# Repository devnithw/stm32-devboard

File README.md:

# STM32 Development board

This project contains KiCAD project files for a custom STM32 development board PCB which uses the STM32F103C8Tx microcontroller.

## Schematic design
The PCB schematic file for development board is contained in the file `stm32_board.kicad_sch`. The following is a screenshot of the schematic. 

The development board uses the `STM32F103C8Tx` microcontroller. USB interface is used for both power supply and serial communication. The power fdrom the USB interface is regulated to +3.3V using the regulator circuit. An High Speed External clock is used for 16 MHz operation. The board includes pin header ports for UART and I2C communication also.

## PCB design
The PCB layout file for the circuit is contained in `stm32_board.kicad_pcb` file. Below is the screenshot of the final PCB layout after routing. I have included mounting holes for the board to be mounted onto a enclosure. The footprints for most of the components have been used from the KiCAD library itself. 3D view for the USB port was downloaded from the manufaturer's website as a step file. It is included in the file `629105150521 (rev1).stp`. I have added male headers for the UART, Serial Wire Debug and I2C communication ports. These can be configured using the STM32 Cube IDE software. 

Shown below is the 3D view of the routed and finalized PCB.

This project was done following the Udemy course by Philip Salmony. [Reference](https://www.udemy.com/course/learn-kicad-v6-and-stm32-hardware-design/)

## Technologies Used
- KiCAD V7
- STM32

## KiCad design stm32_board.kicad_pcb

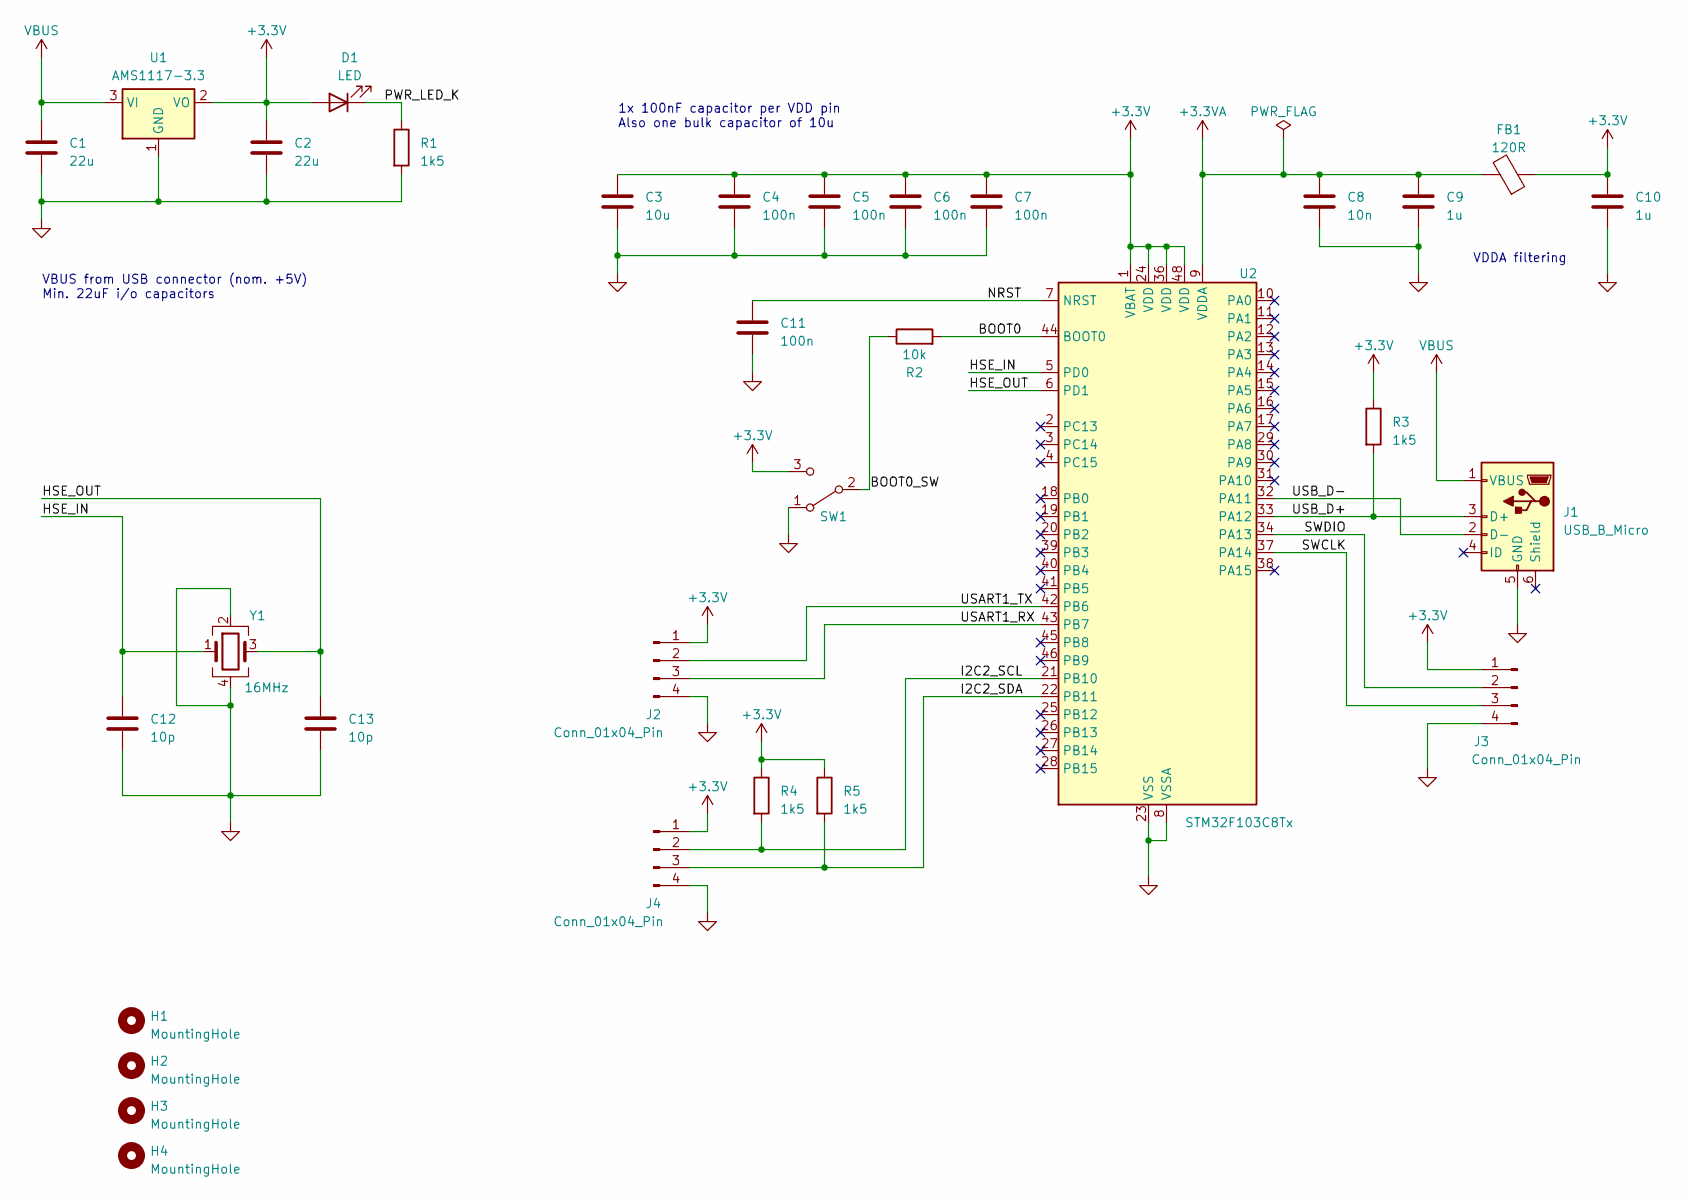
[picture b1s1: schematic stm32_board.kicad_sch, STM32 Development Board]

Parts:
C1, C2: 22u; C_0805_2012Metric
C3: 10u; C_0603_1608Metric
C4, C5, C6, C7, C11: 100n; C_0402_1005Metric
C8: 10n; C_0402_1005Metric
C9, C10: 1u; C_0402_1005Metric
C12, C13: 10p; C_0402_1005Metric
D1: LED; LED_0603_1608Metric
FB1: 120R; L_0603_1608Metric
H1, H2, H3, H4: MountingHole; MountingHole_2.2mm_M2
J1: USB_B_Micro; USB_Micro-B_Wuerth_629105150521
J2, J3, J4: Conn_01x04_Pin; PinHeader_1x04_P2.54mm_Vertical
R1, R3, R4, R5: 1k5; R_0402_1005Metric
R2: 10k; R_0402_1005Metric
SW1: SW_SPDT; SW_SPDT_PCM12
U1: AMS1117-3.3; SOT-223-3_TabPin2
U2: STM32F103C8Tx; LQFP-48_7x7mm_P0.5mm
Y1: 16MHz; Crystal_SMD_3225-4Pin_3.2x2.5mm

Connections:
+3.3V: C2.1, C3.1, C4.1, C5.1, C6.1, C7.1, C10.1, D1.2 (A), FB1.1, J2.1, J3.1, J4.1, R3.1, R4.1, R5.1, SW1.3 (C), U1.2 (VO), U2.1 (VBAT), U2.24 (VDD), U2.36 (VDD), U2.48 (VDD)
+3.3VA: C8.1, C9.1, FB1.2, U2.9 (VDDA)
/BOOT0: R2.2, U2.44 (BOOT0)
/BOOT0_SW: R2.1, SW1.2 (B)
/HSE_IN: C12.1, U2.5 (PD0), Y1.1
/HSE_OUT: C13.1, U2.6 (PD1), Y1.3
/I2C2_SCL: J4.2, R4.2, U2.21 (PB10)
/I2C2_SDA: J4.3, R5.2, U2.22 (PB11)
/NRST: C11.1, U2.7 (NRST)
/PWR_LED_K: D1.1 (K), R1.1
/SWCLK: J3.3, U2.37 (PA14)
/SWDIO: J3.2, U2.34 (PA13)
/USART1_RX: J2.3, U2.43 (PB7)
/USART1_TX: J2.2, U2.42 (PB6)
/USB_D+: J1.3 (D+), R3.2, U2.33 (PA12)
/USB_D-: J1.2 (D-), U2.32 (PA11)
GND: C1.2, C2.2, C3.2, C4.2, C5.2, C6.2, C7.2, C8.2, C9.2, C10.2, C11.2, C12.2, C13.2, J1.5 (GND), J2.4, J3.4, J4.4, R1.2, SW1.1 (A), U1.1 (GND), U2.8 (VSSA), U2.23 (VSS), U2.35 (VSS), U2.47 (VSS), Y1.2, Y1.4
VBUS: C1.1, J1.1 (VBUS), U1.3 (VI)

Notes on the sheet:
1x 100nF capacitor per VDD pin Also one bulk capacitor of 10u
VBUS from USB connector (nom. +5V) Min. 22uF i/o capacitors
VDDA filtering

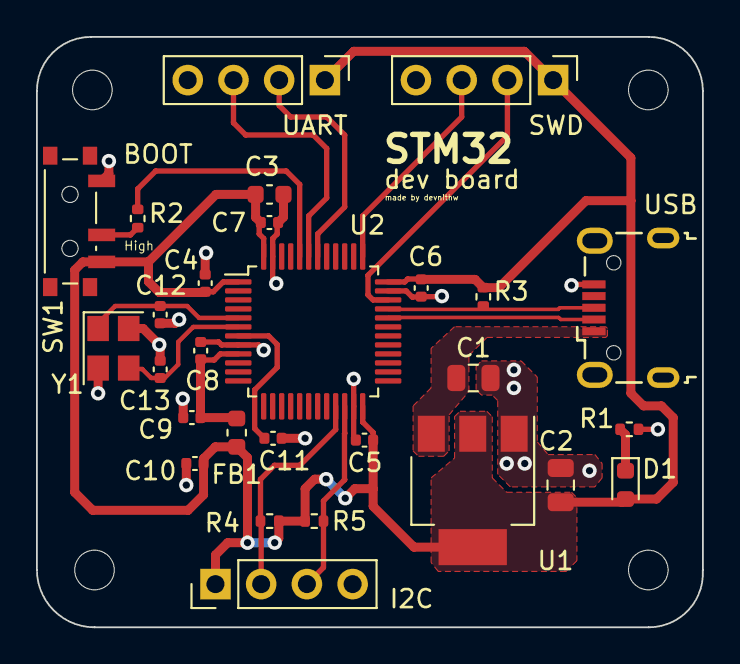
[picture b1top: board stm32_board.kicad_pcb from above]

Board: 2 copper layers, 37.0 x 32.8 mm, 32 parts (0 on the bottom side), 18 nets.

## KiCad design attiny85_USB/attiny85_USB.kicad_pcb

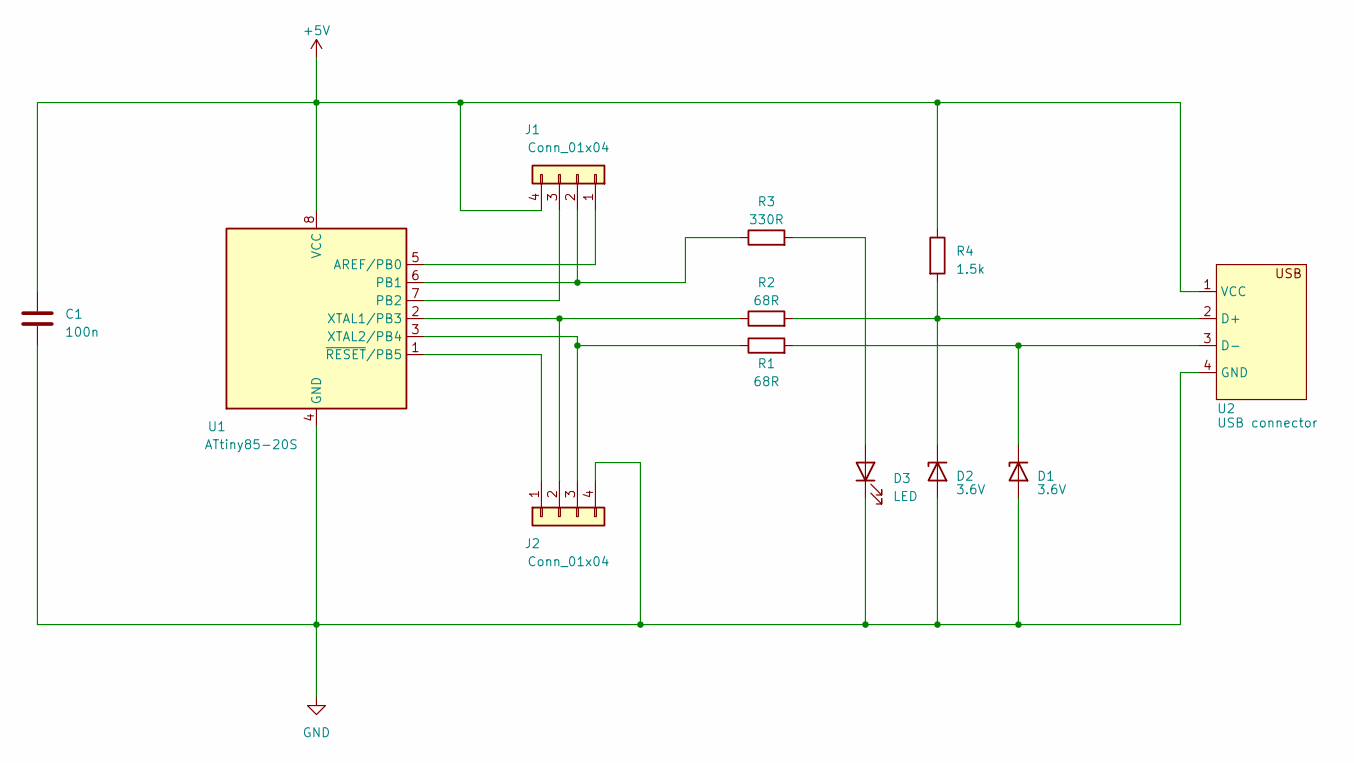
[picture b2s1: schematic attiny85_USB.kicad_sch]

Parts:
C1: 100n; C_1206_3216Metric_Pad1.33x1.80mm_HandSolder
D1, D2: 3.6V; D_SOD-123
D3: LED; LED_1206_3216Metric_Pad1.42x1.75mm_HandSolder
J1, J2: Conn_01x04; PinHeader_1x04_P2.54mm_Vertical
R1, R2: 68R; R_0805_2012Metric_Pad1.20x1.40mm_HandSolder
R3: 330R; R_0805_2012Metric_Pad1.20x1.40mm_HandSolder
R4: 1.5k; R_0805_2012Metric_Pad1.20x1.40mm_HandSolder
U1: ATtiny85-20S; SOIC-8W_5.3x5.3mm_P1.27mm
U2: USB connector; usb_connector

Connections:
+5V: C1.1, J1.4, R4.1, U1.8 (VCC), U2.1 (VCC)
GND: C1.2, D1.2 (A), D2.2 (A), D3.1 (K), J2.4, U1.4 (GND), U2.4 (GND)
unnamed: D1.1 (K), R1.2, U2.3 (D-)
unnamed: D2.1 (K), R2.2, R4.2, U2.2 (D+)
unnamed: D3.2 (A), R3.2
unnamed: J1.1, U1.5 (AREF/PB0)
unnamed: J1.2, R3.1, U1.6 (PB1)
unnamed: J1.3, U1.7 (PB2)
unnamed: J2.1, U1.1 (~RESET/PB5)
unnamed: J2.2, R2.1, U1.2 (XTAL1/PB3)
unnamed: J2.3, R1.1, U1.3 (XTAL2/PB4)

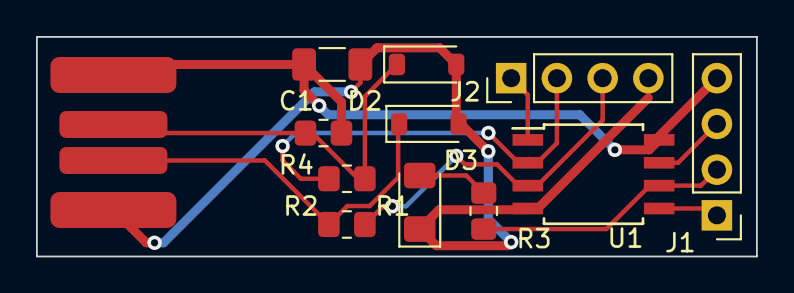
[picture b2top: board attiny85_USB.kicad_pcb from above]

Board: 2 copper layers, 40.0 x 12.2 mm, 12 parts (0 on the bottom side), 11 nets.

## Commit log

2024-05-10 Added first project
2024-05-11 Added STM32 blue pill schematic
2024-05-11 Updated gitignore
2024-05-12 Added Bootloader switch
2024-05-15 Removed other folders
2024-05-15 Updated folder structure
2024-05-15 Added Crystal Oscillator
2024-05-15 Added USB jack
2024-05-15 Added connectors
2024-05-19 Added notes + fixed annotations
2024-05-19 Added footprints
2024-05-19 Added image, updated README
2024-05-22 Updated PCB and added step file
2024-05-22 Updated PCB
2024-05-23 Finished PCB routing
